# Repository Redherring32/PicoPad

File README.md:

# PicoPad
The world's smallest functional NES controller

## Repository Structure:
* Board Files: Contains all files necessary to open the project in KiCad, as well as the schematic and schematic symbols

* 3D-CAD: Contains the source CAD files for the housing design

* PicoPad.pretty: Library of all the custom footprints used on the board

## License:
Licensed under the TAPR Open Hardware License (www.tapr.org/OHL)

©Redherring32 2020

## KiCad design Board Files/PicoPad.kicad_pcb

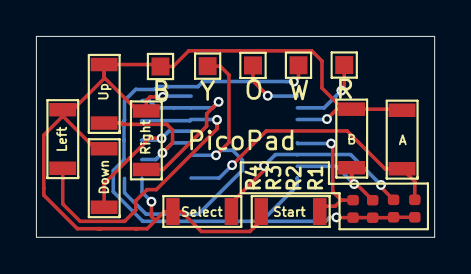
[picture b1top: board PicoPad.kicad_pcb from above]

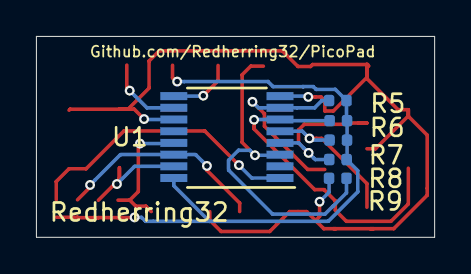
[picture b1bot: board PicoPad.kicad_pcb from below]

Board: 2 copper layers, 22.1 x 11.2 mm, 23 parts (6 on the bottom side), 13 nets.

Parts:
A1: SW_Push; MiniSwitch
B1: SW_Push; MiniSwitch
Brown1: TestPoint_Pad_1.0x1.0mm
D1: SW_Push; MiniSwitch
L1: SW_Push; MiniSwitch
Orange1: TestPoint_Pad_1.0x1.0mm
R1, R2, R3, R4, R5, R6, R7, R8, R9: 1K; R_0402_1005Metric
Red1: TestPoint_Pad_1.0x1.0mm
Right1: SW_Push; MiniSwitch
SL1: SW_Push; MiniSwitch
ST1: SW_Push; MiniSwitch
U1: CD4021BE; TSSOP-16_4.4x5mm_P0.65mm
U2: SW_Push; MiniSwitch
White1: TestPoint_Pad_1.0x1.0mm
Yellow1: TestPoint_Pad_1.0x1.0mm

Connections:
/5V: R1.1, R2.1, R3.1, R4.1, R5.1, R6.1, R7.1, R8.1, U1.16, White1.1
/Clock: Red1.1, U1.10
/Data: R9.1, U1.3, Yellow1.1
/GND: A1.1, B1.1, Brown1.1, D1.1, L1.1, R9.2, Right1.1, SL1.1, ST1.1, U1.8, U1.11, U2.1
/Strobe: Orange1.1, U1.9
unnamed: A1.2, R1.2, U1.1
unnamed: B1.2, R3.2, U1.15
unnamed: D1.2, R7.2, U1.5
unnamed: L1.2, R6.2, U1.6
unnamed: R2.2, SL1.2, U1.14
unnamed: R4.2, ST1.2, U1.13
unnamed: R8.2, U1.4, U2.2
unnamed: R5.2, Right1.2, U1.7

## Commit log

2020-12-08 Cleaned everything up for release
2020-12-09 Add image to readme
2020-12-09 Add labels to schematic
2020-12-09 Improve readme
2023-05-29 + Added Housing CAD!
